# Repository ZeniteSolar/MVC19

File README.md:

# MVC19
**M**ódulo **V**oltímetro **C**an 2019

Embarcação Guarapuvu II

Equipe Zênite Solar

###  Sobre

Este módulo é responsável por exibir os principais parâmetros do sistema para o piloto em um display OLED de 0,96" (SSD1306).

#### Requisitos e Abordagens
1. Adquirir os parâmetros relevantes da rede CAN

2. Filtragem dos dados
	- Utilizar o ID de cada módulo desejado
	- Conferir se o módulo está enviando informações corretamente, sinalizando em caso de falhas.

3. Formatação para exibição no display
	- Separar os dados conforme display conectado
	
	- Utilização de fonte visível para o piloto
	
	- Criação de layout que facilite leitura rápida dos dados

## Informações exibidas nos displays

------

#### Display 1

​	Informações de Tensão em cada uma das 3 baterias principais.

​	

#### Display 2

​	Corrente de entrada e saída do sistema.

​	RPM do motor.

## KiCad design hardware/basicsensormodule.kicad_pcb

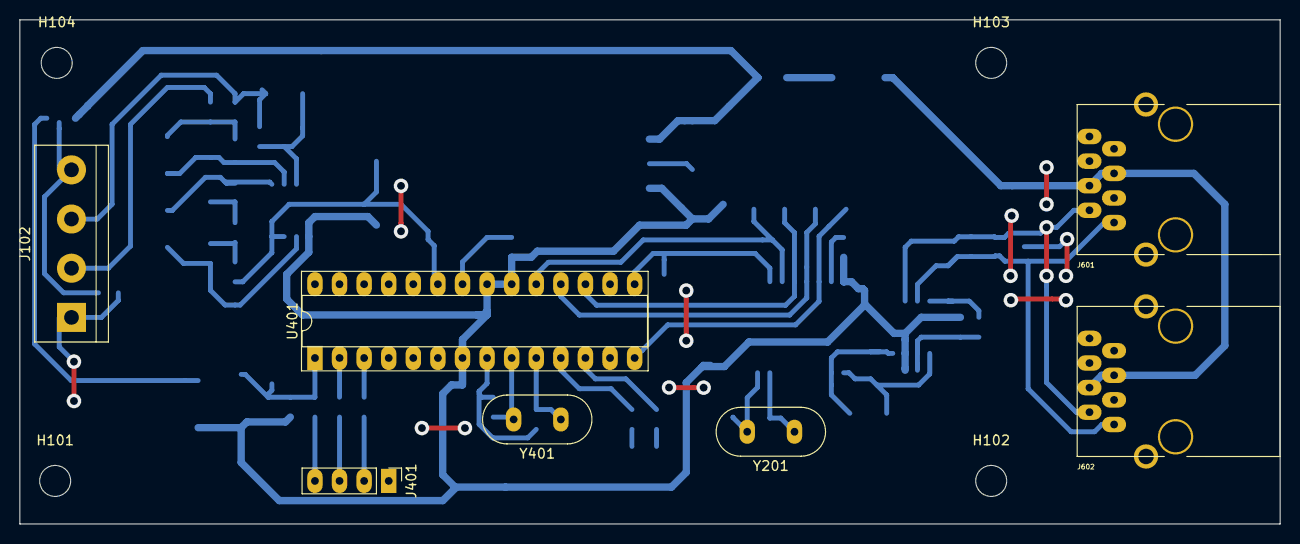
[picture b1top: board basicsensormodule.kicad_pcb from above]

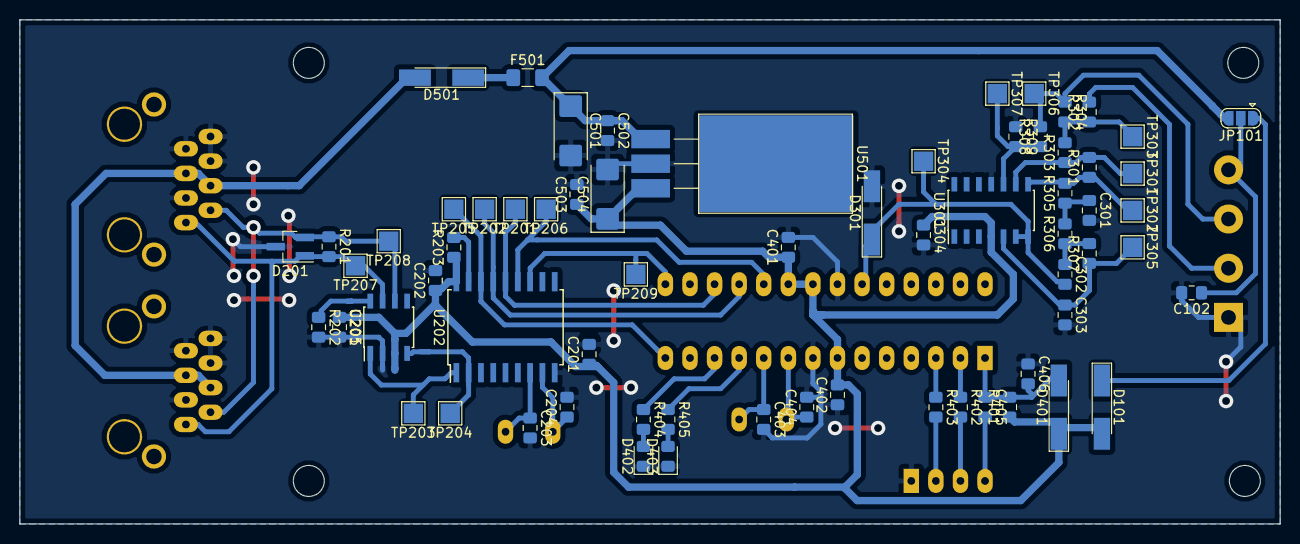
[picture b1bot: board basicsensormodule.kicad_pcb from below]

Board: 2 copper layers, 130.2 x 52.1 mm, 77 parts (66 on the bottom side), 42 nets.

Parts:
C102, C201, C202, C205, C401, C402, C405, C406, C502, C503: 100nF; C_0805_2012Metric_Pad1.15x1.40mm_HandSolder
C203, C204, C403, C404: 22pF; C_0805_2012Metric_Pad1.15x1.40mm_HandSolder
C301, C302, C303, C304: 100n; C_0805_2012Metric_Pad1.15x1.40mm_HandSolder
C501, C504: 1uF; CP_EIA-6032-20_AVX-F_Pad2.25x2.35mm_HandSolder
D101, D401, D501: LL4148; D_MiniMELF_Handsoldering
D201: pesd1can; SOT-23_Handsoldering
D301: 4V7; D_MiniMELF_Handsoldering
D402, D403: LED_RED; LED_0805_2012Metric_Pad1.15x1.40mm_HandSolder
F501: 500mA; Fuse_1206_3216Metric_Pad1.42x1.75mm_HandSolder
H101, H102, H103, H104: MountingHole; MountingHole_3.2mm_M3
J102: SENSOR; TerminalBlock_bornier-4_P5.08mm
J401: USART; PinHeader_1x04_P2.54mm_Vertical
J601, J602: RJ45; RJ45_YH59_01
JP101: jmp; SolderJumper-3_P1.3mm_Open_RoundedPad1.0x1.5mm
R201: 120; R_0805_2012Metric_Pad1.15x1.40mm_HandSolder
R202: 4k7; R_0805_2012Metric_Pad1.15x1.40mm_HandSolder
R203, R301, R303, R304, R308, R309, R401: 10k; R_0805_2012Metric_Pad1.15x1.40mm_HandSolder
R302: 100k; R_0805_2012Metric_Pad1.15x1.40mm_HandSolder
R305, R306, R307, R402, R403, R404, R405: 1k; R_0805_2012Metric_Pad1.15x1.40mm_HandSolder
TP201: SI; TestPoint_Pad_2.0x2.0mm
TP202: SO; TestPoint_Pad_2.0x2.0mm
TP203: TXCAN; TestPoint_Pad_2.0x2.0mm
TP204: RXCAN; TestPoint_Pad_2.0x2.0mm
TP205: SC; TestPoint_Pad_2.0x2.0mm
TP206: SCK; TestPoint_Pad_2.0x2.0mm
TP207: CAN_H; TestPoint_Pad_2.0x2.0mm
TP208: CAN_L; TestPoint_Pad_2.0x2.0mm
TP209: INT; TestPoint_Pad_2.0x2.0mm
TP301: op_a_in-; TestPoint_Pad_2.0x2.0mm
TP302: op_a_out; TestPoint_Pad_2.0x2.0mm
TP303: in-; TestPoint_Pad_2.0x2.0mm
TP304: op_b_out; TestPoint_Pad_2.0x2.0mm
TP305: op_b_in+; TestPoint_Pad_2.0x2.0mm
TP306: in+; TestPoint_Pad_2.0x2.0mm
TP307: op_a_in+; TestPoint_Pad_2.0x2.0mm
U201: MCP2551-I/SN; SOIC-8_3.9x4.9mm_P1.27mm
U202: MCP2515-xSO; SOIC-18W_7.5x11.6mm_P1.27mm
U301: LM324; SOIC-14_3.9x8.7mm_P1.27mm
U401: ATMEGA328P-PU; DIP-28_W7.62mm_Socket
U501: LM7805; TO-220-3_Horizontal_TabDown_SMD
Y201, Y401: 16MHz; Crystal_HC49-U_Vertical

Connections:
+5V: C201.1, C202.1, C205.1, C304.1, C401.1, C402.2, C503.1, C504.1, D101.2, D401.1, R203.1, R401.1, U201.3, U202.18, U301.4, U401.7, U401.20, U401.21, U501.3
/CANBUS CONN/CAN_H: D201.1, J601.1, J602.1, R201.2, TP207.1, U201.7
/CANBUS CONN/CAN_L: D201.2, J601.2, J602.2, R201.1, TP208.1, U201.6
/CANBUS/CS: TP205.1, U202.16, U401.14
/CANBUS/INT: TP209.1, U202.12, U401.15
/CANBUS/RXCAN: TP204.1, U201.4, U202.2
/CANBUS/TXCAN: TP203.1, U201.1, U202.1
/MCU/LED1: R405.1, U401.11
/MCU/LED2: R404.1, U401.12
/MCU/RESET: C405.1, C406.2, D401.2, R401.2, U401.1
/MCU/USART_RX: R402.1, U401.2
/MCU/USART_TX: R403.1, U401.3
/MCU/analog1: C302.2, D301.1, TP304.1, U301.6, U301.7, U401.23
/MISO: TP202.1, U202.15, U401.18
/MOSI: TP201.1, U202.14, U401.17
/OPAMP/in1+: J102.3, R304.1, R308.2, TP306.1
/OPAMP/in1-: J102.2, R302.2
/POWER SUPPLY/+18V_IN: D501.2, J601.4, J601.5, J602.4, J602.5
/POWER SUPPLY/+18V_OUT: C501.1, C502.1, F501.2, JP101.3, U501.1
/SCK: TP206.1, U202.13, U401.19
GND: C102.2, C201.2, C202.2, C203.2, C204.2, C205.2, C301.2, C303.2, C304.2, C401.2, C402.1, C403.2, C404.2, C406.1, C501.2, C502.2, C503.2, C504.2, D201.3, D301.2, D402.1, D403.1, J102.1, J401.1, J601.3, J601.6, J601.7, J601.8, J602.3, J602.6, J602.7, J602.8, R202.2, R309.1, U201.2, U202.9, U301.11, U401.8, U401.22, U501.2
unnamed: C102.1, J102.4, JP101.2
unnamed: C203.1, U202.7, Y201.1
unnamed: C204.1, U202.8, Y201.2
unnamed: C301.1, R305.1, R306.2
unnamed: C302.1, R306.1, R307.2
unnamed: C303.1, R307.1, TP305.1, U301.5
unnamed: C403.1, U401.10, Y401.1
unnamed: C404.1, U401.9, Y401.2
unnamed: C405.2, J401.4
unnamed: D101.1, JP101.1
unnamed: D402.2, R404.2
unnamed: D403.2, R405.2
unnamed: D501.1, F501.1
unnamed: J401.2, R403.2
unnamed: J401.3, R402.2
unnamed: R202.1, U201.8
unnamed: R203.2, U202.17
unnamed: R301.1, R305.2, TP302.1, U301.8
unnamed: R301.2, R303.1, TP301.1, U301.9
unnamed: R302.1, R303.2, R304.2, TP303.1
unnamed: R308.1, R309.2, TP307.1, U301.10

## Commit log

2019-03-30 adding files
2019-03-31 testing
2019-04-09 adding MSC19 state
2019-04-10 DISPLAYS libs added
2019-04-10 ssd1306_avr static lib added
2019-04-10 cleaned
2019-04-10 an abstraction level for display library
2019-04-10 initial ui module
2019-04-10 link and path fixed
2019-04-10 fonts changed
2019-04-10 initial UI idea
2019-04-11 UI added to main
2019-04-11 UI added
2019-04-11 missing a ;
2019-04-11 simple display init done
2019-04-11 display header added
2019-04-11 display clear wrapper added as a function
2019-04-11 started ui idea
2019-04-11 update wrapper added
2019-04-11 test display header missing
2019-04-11 small fix to display_clear()
2019-04-11 testing MSC19 communication
2019-04-12 a basic layout working with uint16_t
2019-04-12 undefined variables fixed
2019-04-12 working UI
2019-04-12 lib updated
2019-04-12 add untracked files
2019-04-14 layout finalizado
2019-07-24 teste de comunicação
2019-07-24 working
2019-08-04 added ui messages
2019-08-07 MVC perdendo mensagens
2019-08-11 ui update
2019-08-12 Float functions added
2019-08-12 Float function added
2019-08-23 conversao dos valores para float
2019-12-01 DISPLAYS library cleaned
2019-12-01 makefiles updated
2020-01-03 teste com nova lib para display
2020-01-03 modules check added
2020-01-07 mam check, can send state
2020-01-19 display lib updated
2020-01-19 added screen change
2020-01-20 avr-can-lib updated
2020-01-20 can_ids removed, makelibs updated
2020-01-20 makelibs updated
2020-01-20 updating MAB CAN messages
2020-01-20 updating MIC CAN messages
2020-01-20 updating MCS CAN messages
2020-01-20 updating MT CAN messages
2020-01-20 updating MSC CAN messages
2020-01-20 updating MVC CAN messages
2020-01-21 updating MAM and GENERIC CAN messages
2020-01-21 can_app and makelibs updated
2020-01-22 checkpoint
2020-01-23 added low battery warnings
2020-02-14 .gitignore updated
2020-07-13 export 3D and layout images
2021-04-27 undef LEN and PREC
2022-03-13 Use extern modifier to fix duplicated variables being defined on newer GCC
2022-03-13 Update makefiles - build for atmega328p, not atmega328pb
2022-03-13 Fix i2c to build for atmega328p instead atmega328pb
2022-03-13 conf: Fix ifdefs - battery information should not depend on adc.
2022-03-13 machine: Fix missing ending parentesis.
2022-03-13 Fix missing declaration.
2022-03-17 Remove executable flag from display.[hc]
2022-03-17 Tensões do banco exibidas individualmente
2022-03-17 Incluido tacometro no primeiro display
2022-03-17 Alterada taxa de atualização
2022-03-17 machine frequency fix
2022-03-17 fix update display failure and improve frequencies
2022-05-16 DSB2022
2022-05-16 funciona mais ou menos
2022-07-21 Added MDE22 extractors and 'check_without' variable
2022-07-21 Added MDE22 extractors and 'checks_without' variable
2022-07-21 Created MDE22 variables
2022-07-21 Added MDE22 variables: steeringbat voltage, current and tail_position)
2022-07-21 Creatd ui_update for MDE22 variables (steerbar voltage,currnt and tail_position)
2022-07-21 remove hack that repeats only one sensor for all batteries
2022-07-21 Using ttyS8, comment previous ports
2022-07-21 Created MDE22 related functions and variables
2022-07-21 Corrected system_flags to include all merge changes
2022-07-21 Add alive feedback and reset if display have an error
2022-07-21 fix column of update signal
2022-07-21 use lower frequency for more stability
2022-07-21 update i2c frequency
2022-07-21 fix make libs
2022-10-06 Vscale float is adjusted for new MSC messages
2022-10-06 Organization, remove voltage ~gambiarra
2022-10-06 Created if condition for can_filters depending on SIGNATURE_SELF
2022-10-06 stty command
2022-10-07 extract mcc measurements
2022-10-07 Fixed I_SCALE_FLOAT, added VERBOSE_ON_UI
2022-10-07 Fixed V/I slaces, added MDE to ui, creen_toggle prototype
2022-10-07 Added steeringbat_measurements_t struct, added no_comm msg for MDE5,6
2022-10-07 Filters for MIC19 and MDE22
2022-10-07 Created extractors for mde measurements and mic pumps
2022-10-07 Change ports
2022-10-07 Fixed conflicting types for checks_without...
2022-10-07 Comment no longer used MCS extractors
2022-10-07 Add screen MPPT
2022-10-07 Added update_mppt_measurements and MPPT screen layout
2022-10-07 If self=MVC19_2, screen will be CURRENT or MPPT depending on PUMP switches. Goes into idle when changed.
2023-06-01 use message frequency from can ids and fix frequency computation
